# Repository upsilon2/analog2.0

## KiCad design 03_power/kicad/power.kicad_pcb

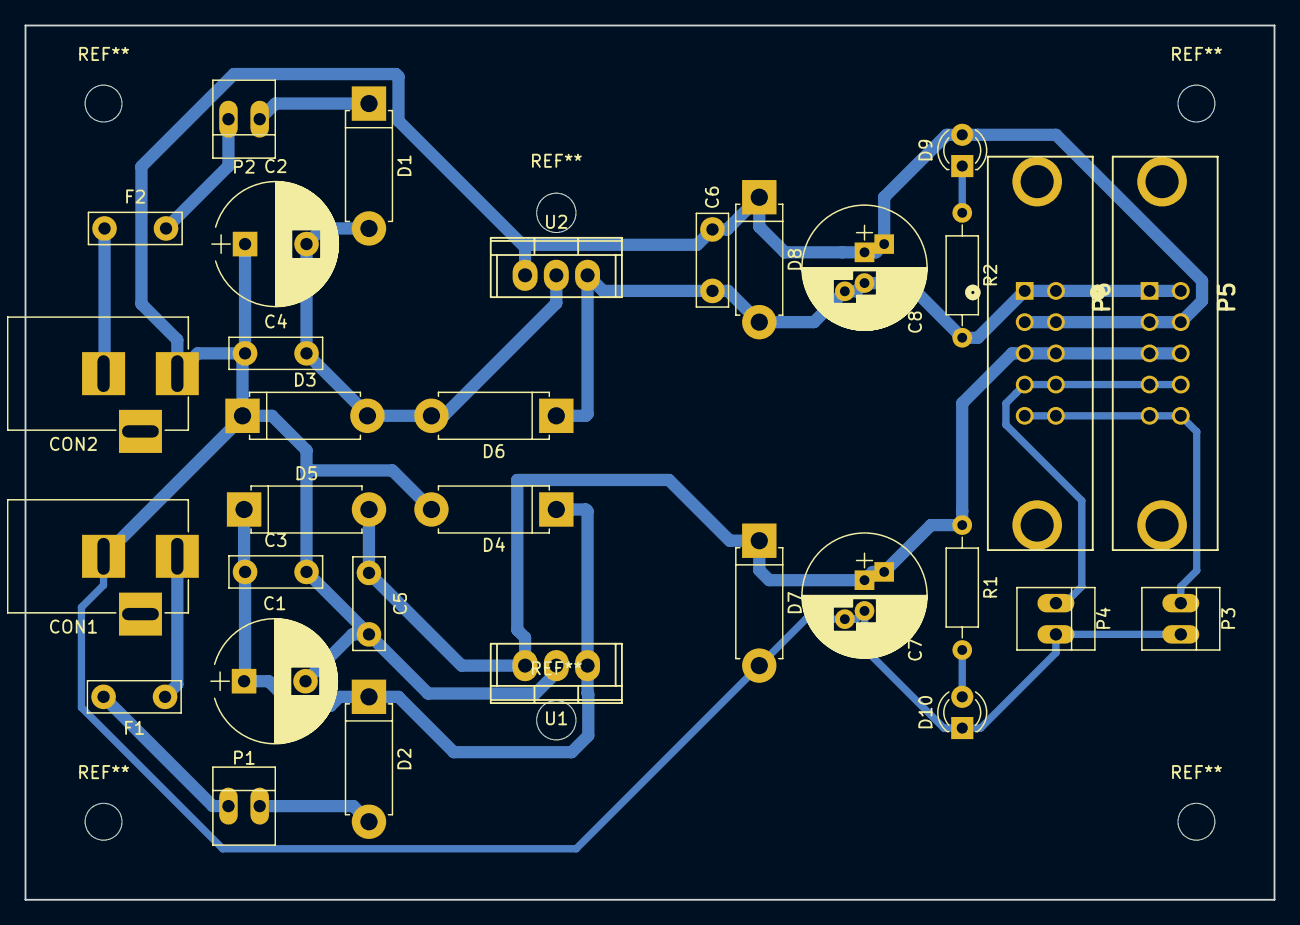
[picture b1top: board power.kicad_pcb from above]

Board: 2 copper layers, 101.6 x 71.1 mm, 32 parts (0 on the bottom side), 15 nets.

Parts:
C1, C2: 220u; CP_Radial_D10.0mm_P5.00mm
C3, C4: 334; C_Disc_D7.5mm_W2.5mm_P5.00mm
C5, C6: 104; C_Disc_D7.5mm_W2.5mm_P5.00mm
C7, C8: 1u; CP_Radial_D10.0mm_P2.50mm_P5.00mm
CON1, CON2: BARREL_JACK
D1, D2, D5, D6: SBD; D_5W_P10.16mm_Horizontal
D3, D4, D7, D8: D; D_5W_P10.16mm_Horizontal
D9, D10: LED; LED_D3.0mm
F1, F2: POLYSW; C_Disc_D7.5mm_W2.5mm_P5.00mm
P1: PW_SW_A; PINHEAD1-2
P2: PW_SW_B; PINHEAD1-2
P3: GATE; PINHEAD1-2
P4: CV; PINHEAD1-2
P5, P6: CONN_02X05; TYCO_5102153-1
R1, R2: 1k; R_Axial_DIN0207_L6.3mm_D2.5mm_P10.16mm_Horizontal
U1: LM7812ACT; TO-220
U2: LM7912CT; TO-220

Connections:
/GND: C1.2, C2.1, C3.2, C4.1, C5.2, C6.1, C7.2, C8.1, CON1.2, CON2.1, D3.1, D4.2, D7.2, D8.1, D9.2, D10.1, P3.2, P4.2, P5.3, P5.4, P6.3, P6.4, U1.2, U2.1
unnamed: C1.1, C3.1, D2.1, D4.1, D5.1, U1.1
unnamed: C2.2, C4.2, D1.2, D3.2, D6.2, U2.2
unnamed: C5.1, C7.1, D5.2, D7.1, P5.5, P5.6, P6.5, P6.6, R1.1, U1.3
unnamed: C6.2, C8.2, D6.1, D8.2, P5.1, P5.2, P6.1, P6.2, R2.2, U2.3
unnamed: CON1.1, F1.1
unnamed: CON2.2, F2.1
unnamed: D1.1, P2.1
unnamed: D2.2, P1.2
unnamed: D9.1, R2.1
unnamed: D10.2, R1.2
unnamed: F1.2, P1.1
unnamed: F2.2, P2.2
unnamed: P3.1, P5.9, P5.10, P6.9, P6.10
unnamed: P4.1, P5.7, P5.8, P6.7, P6.8

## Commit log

2017-11-14 kicad pcb を使用して基板作成を行いたかったので回路はそのままで基板設計をやり直しました。
